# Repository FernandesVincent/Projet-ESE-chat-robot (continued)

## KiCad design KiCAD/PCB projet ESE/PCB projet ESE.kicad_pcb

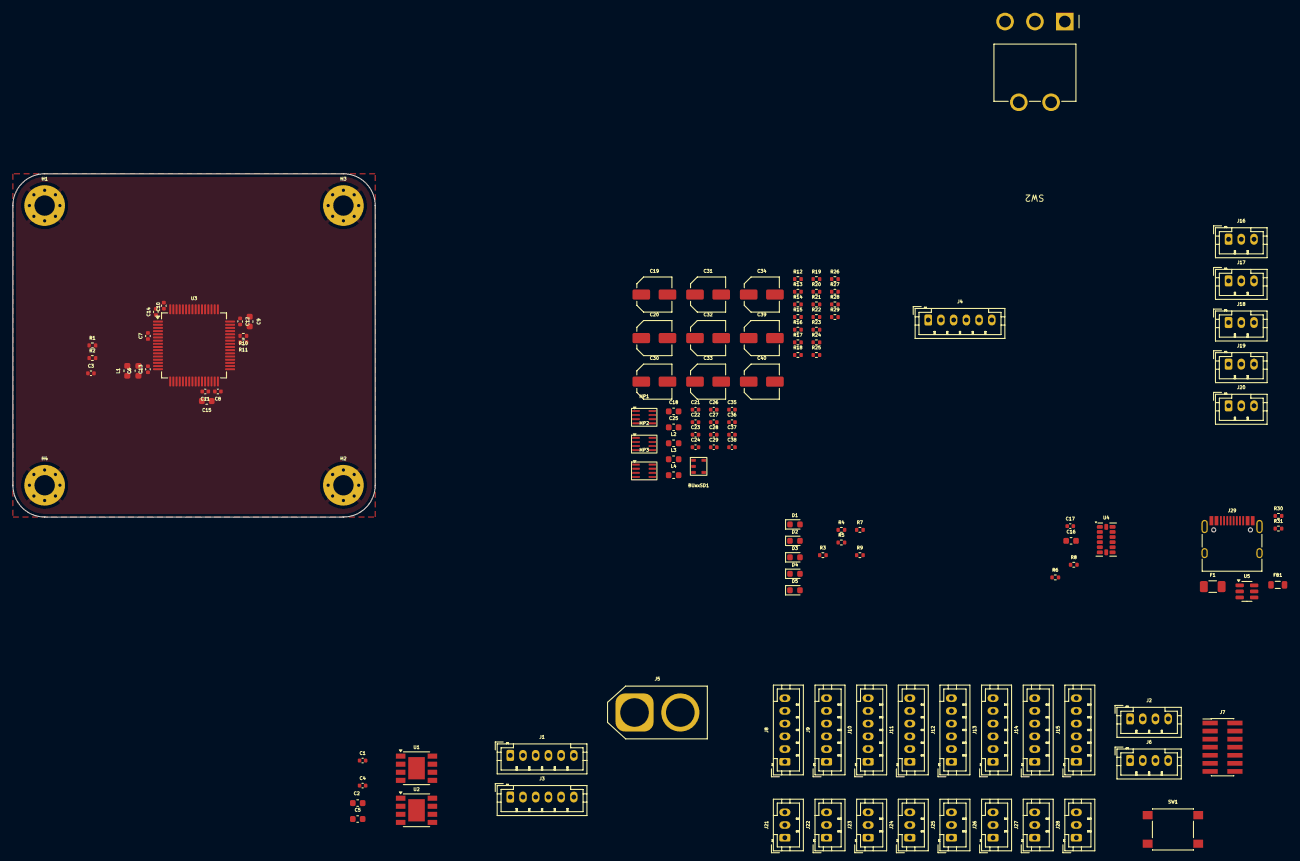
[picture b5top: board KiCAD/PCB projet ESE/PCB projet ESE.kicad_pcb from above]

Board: 4 copper layers, 57.0 x 54.0 mm, 126 parts (0 on the bottom side), 91 nets, no tracks yet.

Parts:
BUxxSD1: SSOP5_BUxxSD5
C1, C3, C4, C7, C8, C10, C11, C12, C13: 100n; C_0402_1005Metric
C2, C5: 4.7u; C_0603_1608Metric
C6: 4u7; C_0603_1608Metric
C9, C15, C16, C18, C25: 1u; C_0603_1608Metric
C14: 10n; C_0402_1005Metric
C17, C21, C22, C23, C24, C26, C27, C35, C36, C37: 0.1u; C_0402_1005Metric
C19, C20, C30, C31, C32, C33, C34, C39, C40: 22u; C_Elec_5x5.4
C28, C29, C38: 15p; C_0402_1005Metric
D1, D2, D3, D4, D5: LED; LED_0603_1608Metric
F1: 250mA; Fuse_1206_3216Metric
FB1: 600 @ 100MHz; L_0805_2012Metric
H1, H2, H3, H4: MountingHole_Pad; MountingHole_3.2mm_M3_Pad_Via
J1, J3, J4, J8, J9, J10, J11, J12, J13, J14, J15: Conn_01x06; JST_PH_B6B-PH-K_1x06_P2.00mm_Vertical
J2, J6: Conn_01x04; JST_PH_B4B-PH-K_1x04_P2.00mm_Vertical
J5: Conn_01x02; AMASS_XT60-M_1x02_P7.20mm_Vertical
J7: Conn_ST_STDC14; PinHeader_2x07_P1.27mm_Vertical_SMD
J16, J17, J18, J19, J20, J21, J22, J23, J24, J25, J26, J27, J28: Conn_01x03; JST_PH_B3B-PH-K_1x03_P2.00mm_Vertical
J29: USB_C_Receptacle_USB2.0_16P; USB_C_Receptacle_HRO_TYPE-C-31-M-12
L1: 39n; L_0603_1608Metric
L2, L3, L4: 4.7u; L_0603_1608Metric
MP1, MP2, MP3: TSOT23-8
R1: 47k; R_0402_1005Metric
R2: 10k; R_0402_1005Metric
R3: 6k55; R_0402_1005Metric
R4: 2k9; R_0402_1005Metric
R5: 1k65; R_0402_1005Metric
R6, R8, R10, R11: 1k; R_0402_1005Metric
R7: 800; R_0402_1005Metric
R9: 550; R_0402_1005Metric
R12, R13, R14, R15, R24, R25: 100k; R_0402_1005Metric
R16, R17, R26: 20; R_0402_1005Metric
R18, R19: 16k; R_0402_1005Metric
R20: 7.68k; R_0402_1005Metric
R21: 4.9k; R_0402_1005Metric
R22, R23, R29: 40.2k; R_0402_1005Metric
R27: 33k; R_0402_1005Metric
R28: 16.3k; R_0402_1005Metric
R30, R31: 5k1; R_0402_1005Metric
SW1: SW_SPST
SW2: 472121010111; SW_Wurth_WS-TOTV_472123020421
U1, U2: ZXBM5210-SP; Diodes_SO-8EP
U3: STM32G474RETx; LQFP-64_10x10mm_P0.5mm
U4: ADXL343; LGA-14_3x5mm_P0.8mm_LayoutBorder1x6y
U5: USBLC6-2SC6; SOT-23-6

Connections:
+2.8V: C38.2, C39.2, C40.2, J8.5, J9.5, J10.5, J11.5, J12.5, J13.5, J14.5, J15.5, L4.2, R9.1, R29.2
+3.3V: BUxxSD1.5 (Vout), C6.1, C8.1, C9.1, C10.1, C11.1, C12.1, C13.1, C14.1, C16.2, C17.1, C25.1, J1.5, J3.5, J6.1, J7.3 (VCC), L1.1, L1.2, R6.1, R7.1, R8.1, R10.1, R11.1, U3.1 (VBAT), U3.16 (VDD), U3.28 (VREF+), U3.29 (VDDA), U3.32 (VDD), U3.48 (VDD), U3.64 (VDD), U4.1 (Vdd_I/O), U4.6 (Vs), U4.7 (~CS)
+5V: BUxxSD1.1 (Vin), C18.1, C28.2, C30.2, C32.2, F1.2, J2.3, J4.2, J6.4, J16.3, J17.3, J18.3, J19.3, J20.3, J21.2, J22.2, J23.2, J24.2, J25.2, J26.2, J27.2, J28.2, L2.2, R5.1, R22.2
+7.5V: C1.1, C2.2, C4.1, C5.2, C29.2, C31.2, C33.2, J1.6, J3.6, L3.2, R4.1, R23.2, U1.2 (VM), U1.3 (VDD), U1.6 (VREF), U2.2 (VM), U2.3 (VDD), U2.6 (VREF)
+14.8V: C19.2, C20.2, C23.2, C24.2, C34.2, C36.2, MP1.2 (IN), MP2.2 (IN), MP3.2 (IN), R1.1, R3.1, R12.1, R13.1, R24.1, SW2.1
ADC: C3.1, R1.2, R2.1, U3.13 (PA1)
Accel SCL: R8.2, U3.40 (PC8), U4.14 (SCL/SCLK)
Accel SDA: R6.2, U3.41 (PC9), U4.13 (SDA/SDI/SDIO)
D+: J29.A6 (D+), J29.B6 (D+), U5.3 (I/O2)
D-: J29.A7 (D-), J29.B7 (D-), U5.1 (I/O1)
EN/SYNC_2.8: MP3.6 (EN/SYNC), R24.2
EN/SYNC_5: MP1.6 (EN/SYNC), R12.2
EN/SYNC_7.5: MP2.6 (EN/SYNC), R13.2
Encodeur Phase B 1: J1.4, U1.7 (OUT2)
Encodeur Phase B 2: J3.4, U2.7 (OUT2)
Encodeur phase A 1: J1.3, U1.1 (OUT1)
Encodeur phase A 2: J3.3, U2.1 (OUT1)
GND: BUxxSD1.2 (GND), C1.2, C2.1, C3.2, C4.2, C5.1, C6.2, C7.2, C8.2, C9.2, C10.2, C11.2, C12.2, C13.2, C14.2, C16.1, C17.2, C18.2, C19.1, C20.1, C21.2, C22.2, C23.1, C24.1, C25.2, C30.1, C31.1, C32.1, C33.1, C34.1, C35.2, C36.1, C39.1, C40.1, D1.1 (K), D2.1 (K), D3.1 (K), D4.1 (K), D5.1 (K), H1.1, H2.1, H3.1, H4.1, J1.1, J1.2, J2.4, J3.1, J3.2, J4.3, J5.1, J6.2, J7.5 (GND), J7.7 (GND), J7.11 (GNDDetect), J8.6, J9.6, J10.6, J11.6, J12.6, J13.6, J14.6, J15.6, J16.1, J17.1, J18.1, J19.1, J20.1, J21.3, J22.3, J23.3, J24.3, J25.3, J26.3, J27.3, J28.3, J29.A1 (GND), J29.A12 (GND), J29.B1 (GND), J29.B12 (GND), J29.S1 (SHIELD), MP1.4 (GND), MP2.4 (GND), MP3.4 (GND), R2.2, R20.2, R21.2, R28.2, R30.2, R31.2, SW1.2 (B), SW2.G1, SW2.G2, U1.8 (GND), U1.9 (GND), U2.8 (GND), U2.9 (GND), U3.15 (VSS), U3.27 (VSSA), U3.31 (VSS), U3.47 (VSS), U3.63 (VSS), U4.2 (GND), U4.4 (GND), U4.5 (GND), U5.2 (GND)
INT: J8.1, J9.1, J10.1, J11.1, J12.1, J13.1, J14.1, J15.1
INT 1: U3.18 (PA4), U4.8 (INT1)
INT 2: U3.19 (PA5), U4.9 (INT2)
Lidar Output: J6.3, U3.20 (PA6)
NRST: C7.1, J7.12 (~RST), SW1.1 (A), U3.7 (PG10)
unnamed: C26.1, R16.2
unnamed: C27.1, R17.2
unnamed: C28.1, R18.1, R20.1, R22.1
unnamed: C29.1, R19.1, R21.1, R23.1
unnamed: C37.1, R26.2
unnamed: C38.1, R27.1, R28.1, R29.1
unnamed: D1.2 (A), R3.2
unnamed: D2.2 (A), R4.2
unnamed: D3.2 (A), R5.2
unnamed: D4.2 (A), R7.2
unnamed: D5.2 (A), R9.2
unnamed: F1.1, FB1.2
unnamed: J5.2, SW2.2
unnamed: J29.A5 (CC1), R30.1
unnamed: J29.B5 (CC2), R31.1
unnamed: MP1.5 (BST), R16.1
unnamed: MP1.8 (FB), R18.2
unnamed: C26.2, L2.1, MP1.3 (SW)
unnamed: C21.1, MP1.7 (VCC), R14.1
unnamed: MP2.5 (BST), R17.1
unnamed: MP2.8 (FB), R19.2
unnamed: C27.2, L3.1, MP2.3 (SW)
unnamed: C22.1, MP2.7 (VCC), R15.1
unnamed: MP3.5 (BST), R26.1
unnamed: MP3.8 (FB), R27.2
unnamed: C37.2, L4.1, MP3.3 (SW)
unnamed: C35.1, MP3.7 (VCC), R25.1
PG_2.8: MP3.1 (PG), R25.2
PG_5: MP1.1 (PG), R14.2
PG_7.5: MP2.1 (PG), R15.2
PWM FWD 1: U1.4 (FWD), U3.61 (PB8)
PWM FWD 2: U2.4 (FWD), U3.38 (PC6)
PWM REV 1: U1.5 (REV), U3.60 (PB7)
PWM REV 2: U2.5 (REV), U3.39 (PC7)
PWM_LED1: J16.2, U3.57 (PB4)
PWM_LED2: J18.2, U3.58 (PB5)
PWM_LED3: J20.2, U3.24 (PB0)
PWM_LED4: J17.2, U3.25 (PB1)
PWM_LED5: J19.2, U3.59 (PB6)
PWM_servo_1: J21.1, U3.8 (PC0)
PWM_servo_2: J23.1, U3.9 (PC1)
PWM_servo_3: J25.1, U3.10 (PC2)
PWM_servo_4: J27.1, U3.11 (PC3)
PWM_servo_5: J22.1, U3.12 (PA0)
PWM_servo_6: J24.1, U3.56 (PB3)
PWM_servo_7: J26.1, U3.30 (PB10)
PWM_servo_8: J28.1, U3.33 (PB11)
SCL TOF: J8.2, J9.2, J10.2, J11.2, J12.2, J13.2, J14.2, J15.2, R11.2, U3.42 (PA8)
SDA TOF: J8.4, J9.4, J10.4, J11.4, J12.4, J13.4, J14.4, J15.4, R10.2, U3.43 (PA9)
SWCLK: J7.6 (JCLK/SWCLK), U3.50 (PA14)
SWDIO: J7.4 (JTMS/SWDIO), U3.49 (PA13)
UART_Debug_RX: J7.13 (VCP_RX), U3.17 (PA3)
UART_Debug_TX: J7.14 (VCP_TX), U3.14 (PA2)
UART_HC05_RX: J4.5, U3.53 (PC11)
UART_HC05_TX: J4.4, U3.52 (PC10)
UART_mp3_RX: J2.1, U3.55 (PD2)
UART_mp3_TX: J2.2, U3.54 (PC12)
USB_DM: U3.45 (PA11), U5.4 (I/O2)
USB_DP: U3.46 (PA12), U5.6 (I/O1)
VBUS: FB1.1, J29.A4 (VBUS), J29.A9 (VBUS), J29.B4 (VBUS), J29.B9 (VBUS), U5.5 (VBUS)
XSHUT_1: J8.3, U3.44 (PA10)
XSHUT_2: J11.3, U3.51 (PA15)
XSHUT_3: J14.3, U3.37 (PB15)
XSHUT_4: J9.3, U3.36 (PB14)
XSHUT_5: J12.3, U3.34 (PB12)
XSHUT_6: J15.3, U3.35 (PB13)
XSHUT_7: J10.3, U3.26 (PB2)
XSHUT_8: J13.3, U3.62 (PB9)

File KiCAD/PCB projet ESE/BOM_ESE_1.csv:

Reference,Qty,Value,Footprint,
BUxxSD1,1,~,Régu:SSOP5_BUxxSD5,
"C1,C3,C4,C7,C8,C10,C11,C12,C13",9,100n,Capacitor_SMD:C_0402_1005Metric,
"C2,C5",2,4.7u,Capacitor_SMD:C_0603_1608Metric,
C6,1,4u7,Capacitor_SMD:C_0603_1608Metric,
"C9,C15,C16,C18,C25",5,1u,Capacitor_SMD:C_0603_1608Metric,
C14,1,10n,Capacitor_SMD:C_0402_1005Metric,
"C17,C21,C22,C23,C24,C26,C27,C35,C36,C37",10,0.1u,Capacitor_SMD:C_0402_1005Metric,
"C19,C20,C30,C31,C32,C33,C34,C39,C40",9,22u,Capacitor_SMD:C_Elec_5x5.4,
"C28,C29,C38",3,15p,Capacitor_SMD:C_0402_1005Metric,
"D1,D2,D3,D4,D5",5,LED,LED_SMD:LED_0603_1608Metric,
F1,1,250mA,Fuse:Fuse_1206_3216Metric,
FB1,1,600 @ 100MHz,Inductor_SMD:L_0805_2012Metric,Wurth
"H1,H2,H3,H4",4,MountingHole_Pad,MountingHole:MountingHole_3.2mm_M3_Pad_Via,
"J1,J3,J4,J8,J9,J10,J11,J12,J13,J14,J15",11,Conn_01x06,Connector_JST:JST_PH_B6B-PH-K_1x06_P2.00mm_Vertical,
"J2,J6",2,Conn_01x04,Connector_JST:JST_PH_B4B-PH-K_1x04_P2.00mm_Vertical,
J5,1,Conn_01x02,Connector_AMASS:AMASS_XT60-M_1x02_P7.20mm_Vertical,
J7,1,Conn_ST_STDC14,Connector_PinHeader_1.27mm:PinHeader_2x07_P1.27mm_Vertical_SMD,
"J16,J17,J18,J19,J20,J21,J22,J23,J24,J25,J26,J27,J28",13,Conn_01x03,Connector_JST:JST_PH_B3B-PH-K_1x03_P2.00mm_Vertical,
J29,1,USB_C_Receptacle_USB2.0_16P,Connector_USB:USB_C_Receptacle_HRO_TYPE-C-31-M-12,
L1,1,39n,Capacitor_SMD:C_0402_1005Metric_Pad0.74x0.62mm_HandSolder,CoilCraft 0603
"L2,L3,L4",3,4.7u,Inductor_SMD:L_0603_1608Metric,CoilCraft 0603
"MP1,MP2,MP3",3,~,Régu:TSOT23-8,
R1,1,47k,Resistor_SMD:R_0402_1005Metric,
R2,1,10k,Resistor_SMD:R_0402_1005Metric,
R3,1,6k55,Resistor_SMD:R_0402_1005Metric,6.49k mais ok car LED
R4,1,2k9,Resistor_SMD:R_0402_1005Metric,2.7k mais ok car LED
R5,1,1k65,Resistor_SMD:R_0402_1005Metric,1.5k mais ok car LED
"R6,R8,R10,R11",4,1k,Resistor_SMD:R_0402_1005Metric,
R7,1,800,Resistor_SMD:R_0402_1005Metric,750 ohm mais ok car LED
R9,1,550,Resistor_SMD:R_0402_1005Metric,510 ohm dans classeur mais ok car LED
"R12,R13,R14,R15,R24,R25",6,100k,Resistor_SMD:R_0402_1005Metric,
"R16,R17,R26",3,20,Resistor_SMD:R_0402_1005Metric,
"R18,R19",2,16k,Resistor_SMD:R_0402_1005Metric,
R20,1,7.68k,Resistor_SMD:R_0402_1005Metric,Vishay
R21,1,4.9k,Resistor_SMD:R_0402_1005Metric,4.99k à vérif
"R22,R23,R29",3,40.2k,Resistor_SMD:R_0402_1005Metric,
R27,1,33k,Resistor_SMD:R_0402_1005Metric,ok classeur
R28,1,16.3k,Resistor_SMD:R_0402_1005Metric,Vishay 16.2k
"R30,R31",2,5k1,Resistor_SMD:R_0402_1005Metric,ok classeur
SW1,1,SW_SPST,Régu:SW_SPST,
SW2,1,SW_SPDT,Régu:SW_SPDT,
"U1,U2",2,ZXBM5210-SP,Package_SO:Diodes_SO-8EP,
U3,1,STM32G474RETx,Package_QFP:LQFP-64_10x10mm_P0.5mm,
U4,1,ADXL343,Package_LGA:LGA-14_3x5mm_P0.8mm_LayoutBorder1x6y,
U5,1,USBLC6-2SC6,Package_TO_SOT_SMD:SOT-23-6,

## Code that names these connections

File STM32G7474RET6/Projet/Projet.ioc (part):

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Mcu.Name=STM32G474R(B-C-E)Tx
Mcu.Package=LQFP64
Mcu.UserName=STM32G474RETx
PA0.Signal=S_TIM5_CH1
PA1.Mode=IN2-Single-Ended
PA1.Signal=ADC1_IN2
PA10.Signal=GPIO_Output
PA11.Signal=S_TIM4_CH1
PA12.Signal=S_TIM4_CH2
PA13.Mode=Serial_Wire
PA13.Signal=SYS_JTMS-SWDIO
PA14.Mode=Serial_Wire
PA14.Signal=SYS_JTCK-SWCLK
PA15.Signal=S_TIM8_CH1
PA2.Mode=Asynchronous
PA2.Signal=USART2_TX
PA3.Mode=Asynchronous
PA3.Signal=USART2_RX
PA4.Signal=S_TIM3_CH2
PA5.Signal=GPIO_Output
PA6.Signal=S_TIM3_CH1
PA7.Signal=GPIO_Output
PA8.Mode=I2C
PA8.Signal=I2C2_SDA
PA9.Mode=I2C
PA9.Signal=I2C2_SCL
PB0.Signal=GPXTI0
PB1.Mode=IN12-Single-Ended
PB1.Signal=ADC1_IN12
PB10.Signal=GPIO_Output
PB11.Signal=GPIO_Output
PB12.Signal=GPXTI12
PB13.Signal=GPXTI13
PB14.Signal=S_TIM15_CH1
PB15.Signal=GPIO_Output
PB2.Mode=IN12-Single-Ended
PB2.Signal=ADC2_IN12
PB3.Mode=PWM Generation1 CH1 CH1N
PB3.Signal=TIM8_CH1N
PB4.Signal=GPXTI4
PB5.Signal=GPXTI5
PB6.Signal=GPXTI6
PB7.Signal=GPXTI7
PB9.Signal=GPXTI9
PC0.Signal=S_TIM1_CH1
PC1.Signal=GPXTI1
PC10.Mode=Asynchronous
PC10.Signal=UART4_TX
PC11.Mode=Asynchronous
PC11.Signal=UART4_RX
PC12.Mode=Asynchronous
PC12.Signal=UART5_TX
PC13.Mode=PWM Generation1 CH1 CH1N
PC13.Signal=TIM1_CH1N
PC14-OSC32_IN.Signal=GPXTI14
PC15-OSC32_OUT.Signal=GPXTI15
PC2.Signal=GPXTI2
PC3.Signal=GPXTI3
PC4.Mode=Half_duplex(single_wire_mode)
PC4.Signal=USART1_TX
PC5.Signal=GPIO_Output
PC6.Mode=I2C
PC6.Signal=I2C4_SCL
PC7.Mode=I2C
PC7.Signal=I2C4_SDA
PC8.Mode=I2C
PC8.Signal=I2C3_SCL
PC9.Mode=I2C
PC9.Signal=I2C3_SDA
PD2.Mode=Asynchronous
PD2.Signal=UART5_RX
PF0-OSC_IN.Mode=HSE-External-Oscillator
PF0-OSC_IN.Signal=RCC_OSC_IN
PF1-OSC_OUT.Mode=HSE-External-Oscillator
PF1-OSC_OUT.Signal=RCC_OSC_OUT
PG10-NRST.Signal=GPXTI10
RCC.HSE_VALUE=8000000
RCC.SYSCLKFreq_VALUE=16000000
board=custom

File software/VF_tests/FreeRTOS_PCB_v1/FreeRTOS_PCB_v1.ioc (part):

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Mcu.Name=STM32G474R(B-C-E)Tx
Mcu.Package=LQFP64
Mcu.UserName=STM32G474RETx
PA1.GPIOParameters=GPIO_Label
PA1.GPIO_Label=ADC_bat
PA1.Mode=IN2-Single-Ended
PA1.Signal=ADC1_IN2
PA13.Mode=Serial_Wire
PA13.Signal=SYS_JTMS-SWDIO
PA14.Mode=Serial_Wire
PA14.Signal=SYS_JTCK-SWCLK
PA2.GPIOParameters=GPIO_Label
PA2.GPIO_Label=UART_LIDAR
PA2.Mode=Half_duplex(single_wire_mode)
PA2.Signal=USART2_TX
PA3.GPIOParameters=GPIO_Label
PA3.GPIO_Label=M_CTRL
PA3.Signal=S_TIM5_CH4
PA4.GPIOParameters=GPIO_Label
PA4.GPIO_Label=INT1
PA4.Signal=GPXTI4
PA5.GPIOParameters=GPIO_Label
PA5.GPIO_Label=XSHUT1
PA5.Signal=GPIO_Output
PA6.GPIOParameters=GPIO_Label
PA6.GPIO_Label=INT2
PA6.Signal=GPXTI6
PA7.GPIOParameters=GPIO_Label
PA7.GPIO_Label=XSHUT2
PA7.Signal=GPIO_Output
PB0.GPIOParameters=GPIO_Label
PB0.GPIO_Label=XSHUT4
PB0.Signal=GPIO_Output
PB1.GPIOParameters=GPIO_Label
PB1.GPIO_Label=INT4
PB1.Signal=GPXTI1
PB10.GPIOParameters=GPIO_Label
PB10.GPIO_Label=INT0
PB10.Signal=GPIO_Output
PB11.GPIOParameters=GPIO_Label
PB11.GPIO_Label=XSHUT5
PB11.Signal=GPIO_Output
PB12.GPIOParameters=GPIO_Label
PB12.GPIO_Label=INT5
PB12.Signal=GPXTI12
PB2.GPIOParameters=GPIO_Label
PB2.GPIO_Label=XSHUT0
PB2.Signal=GPIO_Output
PB4.GPIOParameters=GPIO_Label
PB4.GPIO_Label=PWM_LED
PB4.Signal=S_TIM16_CH1
PB6.GPIOParameters=GPIO_Label
PB6.GPIO_Label=REV2
PB6.Signal=S_TIM4_CH1
PB7.GPIOParameters=GPIO_Label
PB7.GPIO_Label=FWD2
PB7.Signal=S_TIM4_CH2
PB8-BOOT0.GPIOParameters=GPIO_Label
PB8-BOOT0.GPIO_Label=REV1
PB8-BOOT0.Signal=S_TIM8_CH2
PB9.GPIOParameters=GPIO_Label
PB9.GPIO_Label=FWD1
PB9.Signal=S_TIM8_CH3
PC0.GPIOParameters=GPIO_Label
PC0.GPIO_Label=Encodeur1_PhaseB
PC0.Signal=S_TIM1_CH1
PC1.GPIOParameters=GPIO_Label
PC1.GPIO_Label=Encodeur1_PhaseA
PC1.Signal=S_TIM1_CH2
PC10.GPIOParameters=GPIO_Label
PC10.GPIO_Label=UART_ST-LINK_TX
PC10.Mode=Asynchronous
PC10.Signal=UART4_TX
PC11.GPIOParameters=GPIO_Label
PC11.GPIO_Label=UART_ST-LINK_RX
PC11.Mode=Asynchronous
PC11.Signal=UART4_RX
PC12.GPIOParameters=GPIO_Label
PC12.GPIO_Label=UART_MP3_TX
PC12.Mode=Asynchronous
PC12.Signal=UART5_TX
PC4.GPIOParameters=GPIO_Label
PC4.GPIO_Label=INT3
PC4.Signal=GPIO_Output
PC5.GPIOParameters=GPIO_Label
PC5.GPIO_Label=XSHUT3
PC5.Signal=GPIO_Output
PC6.GPIOParameters=GPIO_Label
PC6.GPIO_Label=Encodeur2_PhaseA
PC6.Signal=S_TIM3_CH1
PC7.GPIOParameters=GPIO_Label
PC7.GPIO_Label=Encoder2_PhaseB
PC7.Signal=S_TIM3_CH2
PC8.GPIOParameters=GPIO_Label
PC8.GPIO_Label=I2C_TOF_SCL
PC8.Mode=I2C
PC8.Signal=I2C3_SCL
PC9.GPIOParameters=GPIO_Label
PC9.GPIO_Label=I2C_TOF_SDA
PC9.Mode=I2C
PC9.Signal=I2C3_SDA
PD2.GPIOParameters=GPIO_Label
PD2.GPIO_Label=UART_MP3_RX
PD2.Mode=Asynchronous
PD2.Signal=UART5_RX
PG10-NRST.GPIOParameters=GPIO_Label
PG10-NRST.GPIO_Label=NRST
PG10-NRST.Signal=GPXTI10
RCC.HSE_VALUE=8000000
RCC.SYSCLKFreq_VALUE=16000000
board=custom

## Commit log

2025-09-10 repo
2025-09-10 datasheets
2025-09-10 add diag
2025-09-10 datasheet
2025-09-10 schematic pcb v0
2025-09-11 kicad moteurs
2025-09-11 Diag v2
2025-09-11 Mettre à jour projet ESE.drawio
2025-09-11 Mettre à jour drawio
2025-09-11 maj schematic
2025-09-12 Kicad for Reg Values
2025-09-12 pcb schematic maj
2025-09-14 finish first version of schematic
2025-09-15 maj scgematic
2025-09-15 maj schematic & pinout CubeIDE
2025-09-15 maj schematic et pinout
2025-09-16 First Onshape Draft
2025-09-16 update pcb
2025-09-17 new pinout
2025-09-17 modif pcb editor & sch for new uc pinout
2025-09-17 replace usb c by jst xh
2025-09-18 v1 PCB
2025-09-22 maj pcb and pinout
2025-09-22 code tof avec nucleo
2025-09-22 code tof avec nucleo nettoyé
2025-09-22 code tof avec nucleo en mieux
2025-09-24 maj inductance 4.7uH
2025-09-24 Ajouté(e) Arbo.drawio
2025-09-25 Mettre à jour Arbo.drawio
2025-09-25 maj C25 & C26
2025-09-26 Create Meca_V1
2025-09-26 maj mpn & gitignore
2025-09-26 maj gitignore
2025-09-26 maj datasheet
2025-09-26 maj pinout pcb 2425
2025-09-28 modelisation v1
2025-09-30 v2 meca
2025-09-30 Start for motor
2025-10-01 review pcb
2025-10-01 gerbers
2025-10-01 lidar avec nucleo premier code avec reception uart à interruption ligne IDLE
2025-10-01 started code for motor
2025-10-03 LED NEOPIXEL
2025-10-04 neopxiel + tof v1 ok
2025-10-06 maj GUI
2025-10-06 tof & led v2
2025-10-06 onshape v4
2025-10-07 vazy ca me chier vincent me fait saoul
2025-10-07 avec les commentaires ajoutés
2025-10-09 code Lidar v2
2025-10-10 ControlMotor.h
2025-10-12 update code test
2025-10-12 create rasbpi folder
2025-10-12 uart js code
2025-10-12 add print connect
2025-10-12 require()
2025-10-12 first rasbpi code in cubeIDE
2025-10-12 several test
2025-10-12 test Raspi to Nucleo
2025-10-12 comment
2025-10-12 gitignore for software folders
2025-10-12 some drawings
2025-10-13 print JSON in Rasbpi
2025-10-13 gamepad v0
2025-10-13 Continuing on motors
2025-10-14 gamepad.js
2025-10-20 add BOM with M POMMERY plug-in
2025-10-25 server.js
2025-10-26 GUI preview v0
2025-11-06 test vscode/stm32CubeIDE
2025-11-06 add some drivers
2025-11-06 automatic changes when opening project
2025-11-06 solved
2025-11-08 schematic PCB ampli
2025-11-08 sch v2 ampli
2025-11-08 pcb ampli final 1.0
2025-11-09 gerbers pcb ampli
2025-11-09 forgotten MPN and doc
2025-11-09 fix width
2025-11-10 BOM Ampli
2025-11-12 avec fonciton de detection de cible
2025-11-12 folders & FreeRTOS
2025-11-13 Point à mi-parcours
2025-11-17 Li-Ionholder v1
2025-11-18 code nettoyé
2025-11-18 V1_motor
2025-11-18 fix : free le malloc et du coup ca s'arrete plus au bout de quelques minute
2025-11-18 Pinout Cube MX v1 for PCB v2
2025-11-19 fix le probleme de continuite au niveau 0 degre et 360 degre
2025-11-19 en mieux, avec une nouvelle petite fonctionbonus
2025-11-19 Finished Pinout v2
2025-11-20 Schematic done for PCB v2
2025-11-21 start ADXL
2025-11-21 first version 52*52mm
2025-11-22 new version 47x47mm
2025-11-25 routage en cours
2025-11-25 fix : lidar nucleo amélioration
2025-11-26 TOF polling
2025-11-26 Working on ADXL
2025-11-26 v1.5 PCB finished
2025-12-02 PCB V2 routage v2 finished
2025-12-03 ordered PCB v2
2025-12-03 tof2_nucleo, code pour les nouveaux tof, avec interruption sur seuil
2025-12-03 code tof sur mcu g474
2025-12-03 accel + motor test
2025-12-08 vscode for ancien_pcb
2025-12-08 VF_tests folder
2025-12-08 trying to comput pid
2025-12-09 code tof avec interruption et plusieurs tof
2025-12-09 some little changes
2025-12-09 Accelerometre test
2025-12-10 lecture d'acceleration en interruption
2025-12-10 update ADXL
2025-12-10 TOFs v2
2025-12-11 TOF working polling
2025-12-12 MX for new test project
2025-12-16 accelerometre interruption sur single tap
2025-12-16 avec driver :)))
2025-12-16 test lidar and TOF ok
2025-12-25 better version of Lidar code and begin objects detection
2026-01-09 update accel
2026-01-09 accel and lidar
2026-01-13 motors with ramp
2026-01-14 FreeRTOS for Lidar and Tofs
2026-01-15 remove lidar_g474 project
2026-01-15 remove accelerometre project parce que ca ne fonctionnait pas avec le premier pcb, du coup utiliser le driver de acc_test!!
2026-01-17 last code for the project
2026-01-20 Add software report
    This document provides an overview of the software directory, detailing various tests and configurations related to STM32 projects, including accelerometer setup and LiDAR data processing.
2026-01-22 j'ai remis le code tof_g747
2026-01-23 Enhance README with detailed software descriptions
    Updated the README to provide more detailed explanations of the software components and their functionalities.
2026-01-23 Fix spelling and clarity in README for TOF sensors
    Corrected spelling errors and improved clarity in the TOF sensor configuration section.
2026-01-23 fix readme
2026-01-25 Finish README
2026-01-25 Fix images
2026-01-26 j'ai remis le code tof_g747 parce que je l'aime bien mais j'ai expliqué qu'on l'a pas utilisé au finale dans le readme
